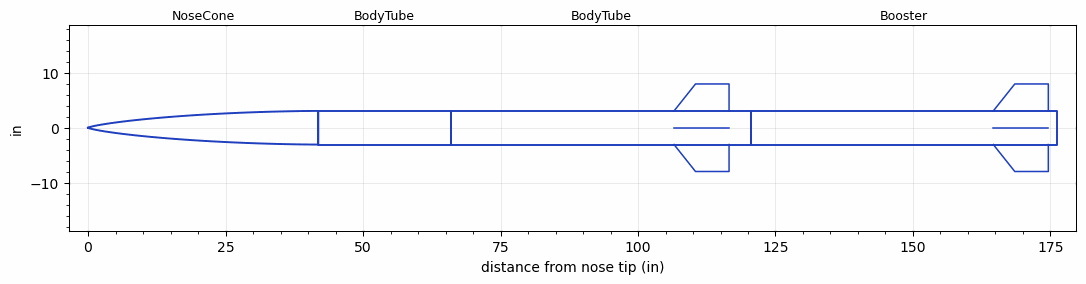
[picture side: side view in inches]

<RASAeroDocument>
 <FileVersion>2</FileVersion>
 <RocketDesign>
  <NoseCone>
   <Length>41.868</Length>
   <Diameter>6.12</Diameter>
   <Shape>LV-Haack</Shape>
   <Location>0</Location>
  </NoseCone>
  <BodyTube>
   <Length>24.043</Length>
   <Diameter>6.12</Diameter>
   <Location>41.868</Location>
  </BodyTube>
  <BodyTube>
   <Length>54.725</Length>
   <Diameter>6.12</Diameter>
   <Location>65.911</Location>
   <Fin>
    <Count>4</Count>
    <Chord>10</Chord>
    <Span>4.9</Span>
    <SweepDistance>3.9</SweepDistance>
    <TipChord>6.1</TipChord>
    <Thickness>0.188</Thickness>
    <Location>14.08</Location>
    <AirfoilSection>Rounded</AirfoilSection>
   </Fin>
  </BodyTube>
  <Booster>
   <Length>55.508</Length>
   <Diameter>6.12</Diameter>
   <InsideDiameter>6.12</InsideDiameter>
   <Location>120.636</Location>
   <ShoulderLength>0</ShoulderLength>
   <Fin>
    <Count>4</Count>
    <Chord>10</Chord>
    <Span>4.9</Span>
    <SweepDistance>3.9</SweepDistance>
    <TipChord>6.1</TipChord>
    <Thickness>0.188</Thickness>
    <Location>11.535</Location>
    <AirfoilSection>Rounded</AirfoilSection>
   </Fin>
  </Booster>
  <Surface>Rough Camouflage Paint</Surface>
  <ModifiedBarrowman>True</ModifiedBarrowman>
  <Turbulence>False</Turbulence>
  <UseBooster1>False</UseBooster1>
  <UseBooster2>False</UseBooster2>
 </RocketDesign>
 <LaunchSite>
  <Altitude>2782</Altitude>
  <Pressure>29.9</Pressure>
  <RodAngle>3</RodAngle>
  <RodLength>22</RodLength>
  <Temperature>110</Temperature>
  <WindSpeed>0</WindSpeed>
 </LaunchSite>
 <Recovery>
  <Altitude1>0</Altitude1>
  <Altitude2>0</Altitude2>
  <DeviceType1>None</DeviceType1>
  <DeviceType2>None</DeviceType2>
  <Event1>False</Event1>
  <Event2>False</Event2>
  <Size1>0</Size1>
  <Size2>0</Size2>
  <EventType1>None</EventType1>
  <EventType2>None</EventType2>
  <CD1>0</CD1>
  <CD2>0</CD2>
 </Recovery>
 <SimulationList>
  <Simulation>
   <SustainerEngine>N1048  (AT/RCS)</SustainerEngine>
   <SustainerLaunchWt>90</SustainerLaunchWt>
   <SustainerNozzleDiameter>2.7</SustainerNozzleDiameter>
   <SustainerCG>77.91</SustainerCG>
   <SustainerIgnitionDelay>4</SustainerIgnitionDelay>
   <Booster1Engine>O3693  (O3693)</Booster1Engine>
   <Booster1LaunchWt>180</Booster1LaunchWt>
   <Booster1SeparationDelay>2</Booster1SeparationDelay>
   <Booster1IgnitionDelay>0</Booster1IgnitionDelay>
   <Booster1CG>126</Booster1CG>
   <Booster1NozzleDiameter>3.5</Booster1NozzleDiameter>
   <IncludeBooster1>True</IncludeBooster1>
   <Booster2Delay>0</Booster2Delay>
   <IncludeBooster2>False</IncludeBooster2>
   <TimetoApogee>63.59713</TimetoApogee>
   <MaxAltitude>48858.23</MaxAltitude>
   <MaxVelocity>1399.37</MaxVelocity>
  </Simulation>
 </SimulationList>
</RASAeroDocument>
